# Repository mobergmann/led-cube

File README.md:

# led-cube

This repository contains:
1. main program: program that runs on the Pi, loads the configuration, and controls the LEDs
2. editor: program to create configuration by yourself
3. assets: files that are relevant for building the cubes
4. documentation: guide on how to assemble the cube, how to compile and install and use the main program and the editor

The documentation can be found in the `doc` folder.
A good entry point to the documentation is the [`doc/README.md`](./doc/README.md) file.

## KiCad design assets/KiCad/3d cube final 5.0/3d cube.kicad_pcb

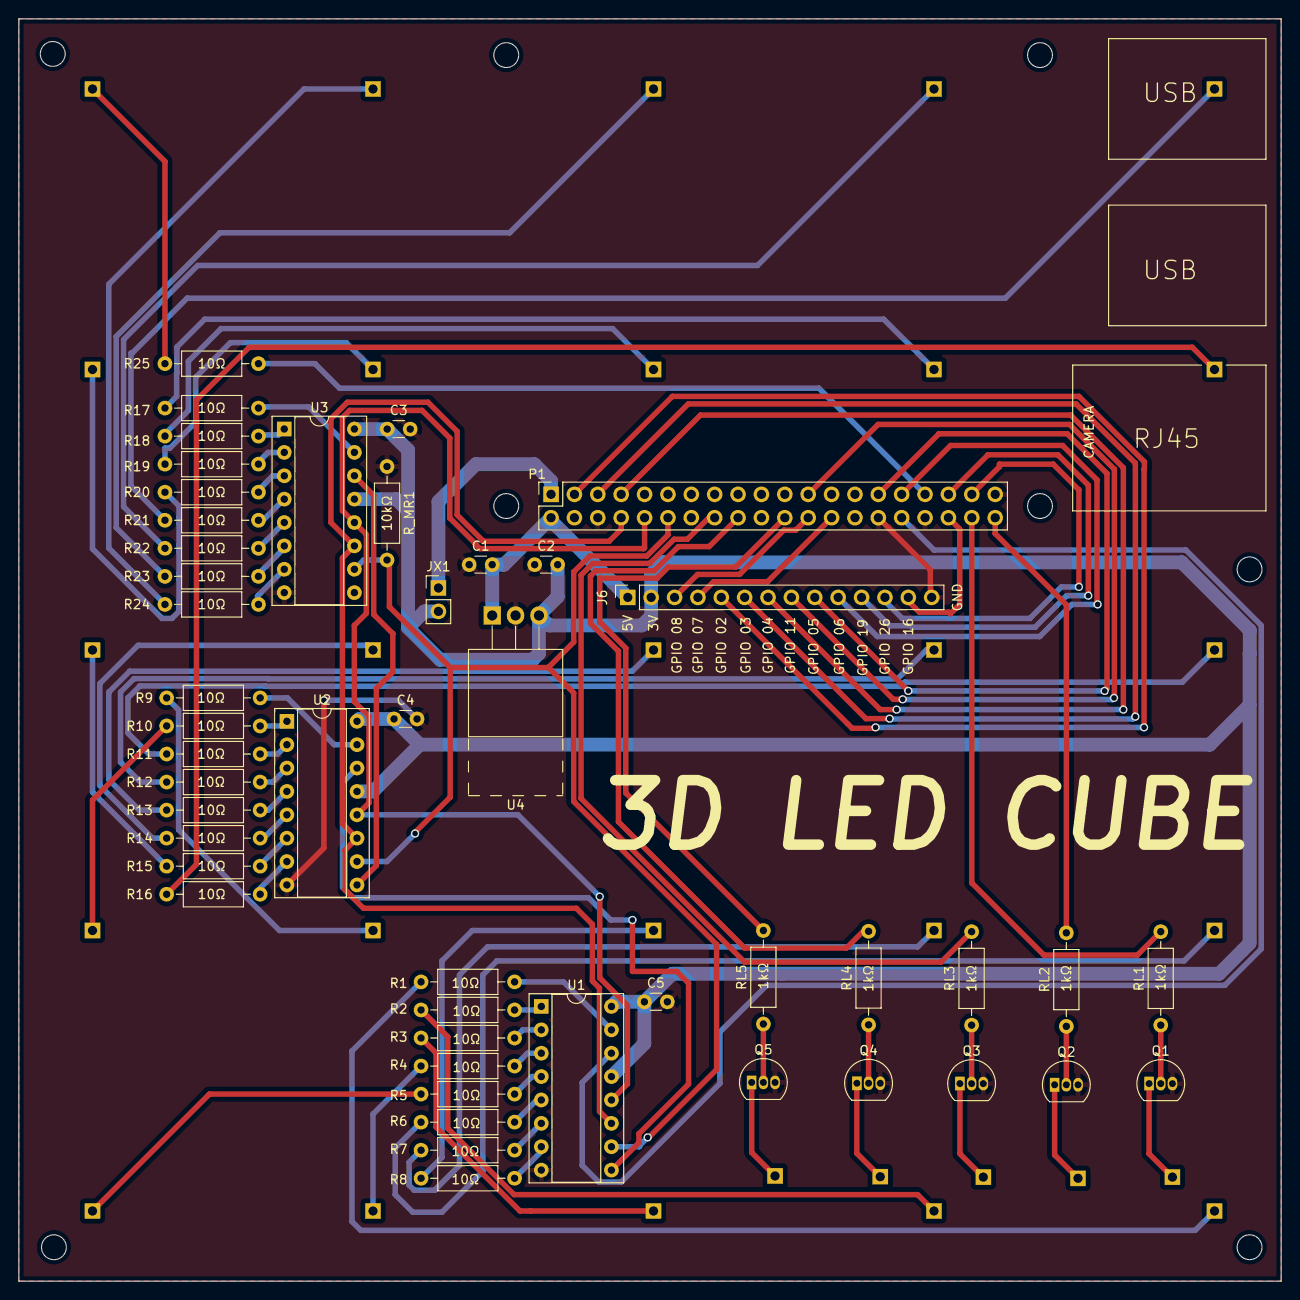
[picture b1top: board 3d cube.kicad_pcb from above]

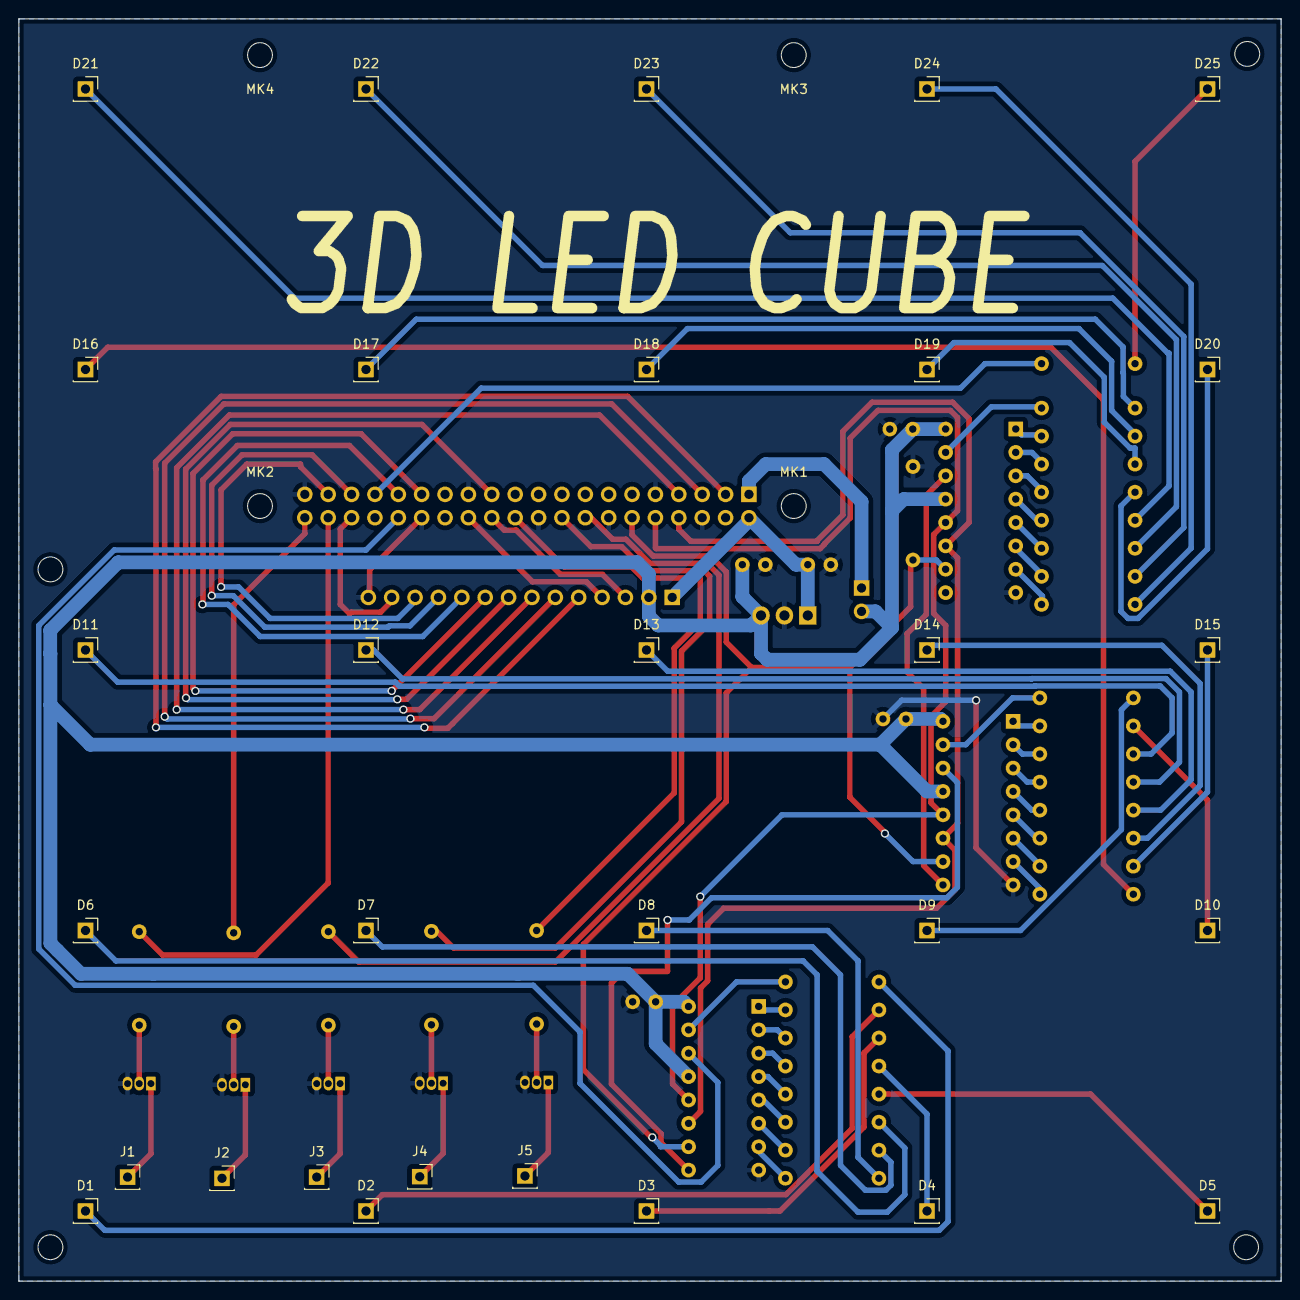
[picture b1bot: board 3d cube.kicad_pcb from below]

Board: 2 copper layers, 137.2 x 137.2 mm, 82 parts (34 on the bottom side), 86 nets.

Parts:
C1: 0.22μF; C_Disc_D3.0mm_W1.6mm_P2.50mm
C2: 10μF; C_Disc_D3.0mm_W1.6mm_P2.50mm
C3, C4, C5: 0.1μF; C_Disc_D3.0mm_W1.6mm_P2.50mm
D1, D2, D3, D4, D5, D6, D7, D8, D9, D10, D11, D12, D13, D14, D15, D16, D17, D18, D19, D20, D21, D22, D23, D24, D25: LED; PinSocket_1x01_P2.54mm_Vertical
J1: First Layer; PinSocket_1x01_P2.54mm_Vertical
J2: Second Layer; PinSocket_1x01_P2.54mm_Vertical
J3: Third Layer; PinSocket_1x01_P2.54mm_Vertical
J4: Fourth Layer; PinSocket_1x01_P2.54mm_Vertical
J5: Fifth Layer; PinSocket_1x01_P2.54mm_Vertical
J6: Conn_01x14_Female; PinSocket_1x14_P2.54mm_Vertical
JX1: 3V Bridge; PinHeader_1x02_P2.54mm_Vertical
MK1, MK2, MK3, MK4: M2.5; MountingHole_2.7mm_M2.5
P1: Conn_02x20_Odd_Even; PinSocket_2x20_P2.54mm_Vertical
Q1, Q2, Q3, Q4, Q5: 2N2222A; TO-92_Inline
R1, R2, R3, R4, R5, R6, R7, R8, R9, R10, R11, R12, R13, R14, R15, R16, R17, R18, R19, R20, R21, R22, R23, R24, R25: 10; R_Axial_DIN0207_L6.3mm_D2.5mm_P10.16mm_Horizontal
RL1, RL2, RL3, RL4, RL5: 1k; R_Axial_DIN0207_L6.3mm_D2.5mm_P10.16mm_Horizontal
R_MR1: 10k; R_Axial_DIN0207_L6.3mm_D2.5mm_P10.16mm_Horizontal
U1, U2, U3: 74HC595; DIP-16_W7.62mm_Socket
U4: LF15_TO220; TO-220-3_Horizontal_TabUp

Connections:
+3.3V: C2.1, C3.1, C4.1, C5.1, J6.2, JX1.2, U1.13 (~OE), U1.16 (VCC), U2.13 (~OE), U2.16 (VCC), U3.13 (~OE), U3.16 (VCC), U4.3 (VO)
+3.3V Rasberry: JX1.1, P1.1, P1.17
+5V: C1.1, J6.1, P1.2, P1.4, U4.1 (VI)
DS: P1.32, U1.14 (SER)
GND: C1.2, C2.2, C3.2, C4.2, C5.2, J6.14, P1.6, P1.9, P1.14, P1.20, P1.25, P1.30, P1.34, P1.39, Q1.3 (C), Q2.3 (C), Q3.3 (C), Q4.3 (C), Q5.3 (C), R_MR1.2, U1.8 (GND), U2.8 (GND), U3.8 (GND), U4.2 (GND)
GPIO2: J6.5, P1.3
GPIO3: J6.6, P1.5
GPIO4: J6.7, P1.7
GPIO5: J6.9, P1.29
GPIO6: J6.10, P1.31
GPIO7: J6.4, P1.26
GPIO8: J6.3, P1.24
GPIO11: J6.8, P1.23
GPIO16: J6.13, P1.36
GPIO19: J6.11, P1.35
GPIO26: J6.12, P1.37
Layer 1: P1.38, RL1.2
Layer 2: P1.40, RL2.2
Layer 3: P1.16, RL3.2
Layer 4: P1.18, RL4.2
Layer 5: P1.22, RL5.2
MR: P1.12, R_MR1.1, U1.10 (~SRCLR), U2.10 (~SRCLR), U3.10 (~SRCLR)
unnamed: D1.1 (K), R1.1
unnamed: D2.1 (K), R2.1
unnamed: D3.1 (K), R3.1
unnamed: D4.1 (K), R4.1
unnamed: D5.1 (K), R5.1
unnamed: D6.1 (K), R6.1
unnamed: D7.1 (K), R7.1
unnamed: D8.1 (K), R8.1
unnamed: D9.1 (K), R9.1
unnamed: D10.1 (K), R10.1
unnamed: D11.1 (K), R11.1
unnamed: D12.1 (K), R12.1
unnamed: D13.1 (K), R13.1
unnamed: D14.1 (K), R14.1
unnamed: D15.1 (K), R15.1
unnamed: D16.1 (K), R16.1
unnamed: D17.1 (K), R17.1
unnamed: D18.1 (K), R18.1
unnamed: D19.1 (K), R19.1
unnamed: D20.1 (K), R20.1
unnamed: D21.1 (K), R21.1
unnamed: D22.1 (K), R22.1
unnamed: D23.1 (K), R23.1
unnamed: D24.1 (K), R24.1
unnamed: D25.1 (K), R25.1
unnamed: J1.1, Q1.1 (E)
unnamed: J2.1, Q2.1 (E)
unnamed: J3.1, Q3.1 (E)
unnamed: J4.1, Q4.1 (E)
unnamed: J5.1, Q5.1 (E)
unnamed: Q1.2 (B), RL1.1
unnamed: Q2.2 (B), RL2.1
unnamed: Q3.2 (B), RL3.1
unnamed: Q4.2 (B), RL4.1
unnamed: Q5.2 (B), RL5.1
unnamed: R1.2, U1.15 (QA)
unnamed: R2.2, U1.1 (QB)
unnamed: R3.2, U1.2 (QC)
unnamed: R4.2, U1.3 (QD)
unnamed: R5.2, U1.4 (QE)
unnamed: R6.2, U1.5 (QF)
unnamed: R7.2, U1.6 (QG)
unnamed: R8.2, U1.7 (QH)
unnamed: R9.2, U2.15 (QA)
unnamed: R10.2, U2.1 (QB)
unnamed: R11.2, U2.2 (QC)
unnamed: R12.2, U2.3 (QD)
unnamed: R13.2, U2.4 (QE)
unnamed: R14.2, U2.5 (QF)
unnamed: R15.2, U2.6 (QG)
unnamed: R16.2, U2.7 (QH)
unnamed: R17.2, U3.15 (QA)
unnamed: R18.2, U3.1 (QB)
unnamed: R19.2, U3.2 (QC)
unnamed: R20.2, U3.3 (QD)
unnamed: R21.2, U3.4 (QE)
unnamed: R22.2, U3.5 (QF)
unnamed: R23.2, U3.6 (QG)
unnamed: R24.2, U3.7 (QH)
unnamed: U1.9 (QH'), U2.14 (SER)
unnamed: U2.9 (QH'), U3.14 (SER)
Pin 25: P1.33, R25.2
SHCP: P1.8, U1.11 (SRCLK), U2.11 (SRCLK), U3.11 (SRCLK)
STCP: P1.10, U1.12 (RCLK), U2.12 (RCLK), U3.12 (RCLK)

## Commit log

2022-06-08 initial
2022-06-17 multiple code bases
2022-06-17 removed build files
2022-06-17 compilable
2022-06-17 notes on which pin used
2022-06-17 gitignore path optimized
2022-06-17 WIP: led software
2022-06-18 added KiCad folder
2022-06-18 converted to class
2022-06-18 removed unnecessary import
2022-06-18 WIP cube UI
2022-06-18 WIP: added UI
2022-06-19 fixed yellow leds
2022-06-19 workable software
2022-06-19 added test-1
2022-06-19 wip: added delta time for max frame time and a test script
2022-06-20 added play sequenze button
2022-06-20 delta time implementation
2022-06-22 rotate with right mouse button, leds in the json files now in the right sequenze
2022-06-22 adjusted to new parser
2022-06-22 removed old targets
2022-06-22 fixed comment messages
2022-06-22 layer test json
2022-06-22 fix json saving
2022-06-22 change data in json to layers
2022-06-22 layer-5 test json
2022-06-22 changed data.json name
2022-06-22 fixed issues (don't know which, look yourself)
2022-06-22 wip: reverse pins and lines
2022-06-23 fixed reverse error
2022-08-03 wip: fixes issues
2022-08-04 added reset test program
2022-08-04 fixed skipp of input
2022-08-05 wip: reset test
2022-08-05 formatted
2022-08-05 reset enhancements
2022-08-05 added dependencies to readme
2022-08-11 added a polling skeleton for pressing buttons
2022-08-11 removed added extra program
2022-08-15 wip readme
2022-08-15 added base project
2022-08-15 added gitignore
2022-08-15 added file documentation
2022-08-15 removed old json files
2022-08-15 ignored clion and vscode files
2022-08-15 moved extra files into assets folder
2022-08-15 renamed notes
2022-08-15 added documentation
2022-08-15 added line numbers to i/o pins
2022-08-15 added Qt3DCore binaries
2022-08-15 added a main window
2022-08-15 added a basic ui (not functional)
2022-08-16 added bluetooth function declaration
2022-08-16 added todo to buttons, which doesnt work
2022-08-17 added bluetooth class
2022-08-17 fixed compilation error
2022-08-17 added is_rising_edge declaration
2022-08-17 added a button test program
2022-08-17 fixed order of pins
2022-08-17 button configuration
2022-08-17 wip: moving files outside
2022-08-18 added blink thread for bluetooth pairing led
2022-08-18 code refactoring
2022-08-18 reset test improvements and fixed an issue in main program
2022-08-18 removed obsolete buttons program
2022-08-19 added threads to cmake linking
2022-08-19 removed buttons from cmake, as file doesn't exists anymore
2022-08-19 removed reset test program
2022-08-19 applied reset to main
2022-08-19 update dependency
2022-08-19 updated readme button pins
2022-08-19 added example json files
2022-08-19 wip: button functionality
2022-08-19 button functionality
2022-08-19 moved reset call to each layer
2022-08-19 changed path to files
2022-08-19 fixed reset
2022-08-19 files are now pulled
2022-08-19 added filesystem to cmake
2022-08-19 added a filesystem test program
2022-08-19 applied the fs test results to main
2022-08-19 removed fs files
2022-08-20 added comment to class member
2022-08-20 added button class
2022-08-20 applied button class to main program
2022-08-20 default led-cube configuration path definition
2022-08-21 wip: cube rendering
2022-08-22 added const to static Button variable
2022-08-22 fixed bluetooth button crashing program
2022-08-22 added cout for cube configuration
2022-08-22 removed exil file
2022-08-22 print first configuration
2022-08-22 restructior falling edge method
2022-08-22 change filepath in cube/main.py add blink_layer.json
2022-08-22 bluetooth order changed, to update after blink
2022-08-22 changed from copy for loop to direct access loop
2022-08-22 added new test files for the cube
2022-08-22 remouve button bounce
2022-08-22 change to falling edge
2022-08-22 finished button bounce
2022-08-22 fixes initialize issues
2022-08-22 removed (sebs) file
2022-08-22 changed order of main methods
2022-08-22 added edge case check and removed iterators from next and previous
2022-08-22 fixed next and previous buttons
2022-08-22 undo: fixed next and previous buttons
2022-08-22 undo: undo: fixed next and previous buttons
2022-08-22 fixed previous button
2022-08-22 fixed accidentally decrementing in next
2022-08-22 added optimisation
2022-08-22 fixed rotation not working
2022-08-22 parsing layout after each button press
2022-08-22 added destructor for main
2022-08-22 removed shadow copy
2022-08-22 removed unnecessary close
2022-08-22 wip: error hunting
2022-08-22 wip: added test program
2022-08-22 wip: test program
2022-08-23 check if the frames have changed and then quit loop
2022-08-23 uncomment reset call in set_leds, as it didn't cause the weird led behaviour
2022-08-23 added print statement and removed revert
2022-08-23 dynamic line name acquisition
2022-08-23 layer python test program
2022-08-23 added input dialogue for test
2022-08-23 added store for cube
2022-08-23 fixed python program
2022-08-23 implemented layer test in c++
2022-08-23 removed print
2022-08-23 fixed layer 5 being enabled
2022-08-23 moved store after turning off layer, so it will be displayed
2022-08-24 wip: does this layer on/ off work?
2022-08-24 git revert to working solution
2022-08-24 sequence test program
2022-08-24 wip: test activation of two pins on two layers
2022-08-24 special pin only turn off on store (with/ like all the other pins)
2022-08-24 wip: hopefully fix all our layer 1 is on and glows, but 5 also glows problems
2022-08-24 reduce the off time to 5 writes
2022-08-24 fixed special pin always on
2022-08-24 fixed array indexing last elem with out-of-bounds
2022-08-24 changed to qt version 6
2022-08-24 removed previous (commented) cmake
2022-08-25 moved from 3d to quick
2022-08-26 added ScrollView for Frames
2022-08-26 rotationiion cube done
2022-08-27 led on/off now functioning
2022-08-27 cube rotation finished
2022-08-27 clean up code
2022-08-27 now going for opengl
2022-08-27 new frame/delete frame button working
2022-08-28 play button working
2022-08-28 clean up
2022-08-28 wip: opengl
2022-08-28 save to JSON works
2022-08-28 preperation for the open button
2022-08-28 open Json button now working/ version 1.0 working
2022-08-29 wip: reverse pins
2022-08-29 wip: removed compilation error
2022-08-29 wip: fixed condition
2022-08-29 wip: loop conditions
2022-08-29 wip: fix segfault
2022-08-29 wip: fix loop performance
2022-08-29 fix orientation to the real cube
2022-08-29 added front indicator
2022-08-29 wip: flipped x- and y-axis
2022-08-29 shift buttons working
2022-08-29 shift button behaviour
2022-08-29 bluetooth class, removed test scripts, still in merge?
2022-08-29 finished random and magic button and copy button
2022-08-30 updated user pin usage in table
2022-08-30 wip: added an installation script file
2022-08-31 moved into src and include folder and deleted test files
2022-08-31 added file-transfer class
2022-08-31 changed data folders moved folder init into main
2022-08-31 removed static from function, because it isn't meant to be
2022-08-31 fixed wrong file paths
2022-08-31 changed file system type in mount to vfat, aka usb
2022-08-31 added function call to update_file_list
2022-08-31 override existing files
2022-08-31 added data to install script
2022-09-02 fixed typo in dependencies
2022-09-05 new file/ WIP gameoflife
2022-09-05 added installation files and assets
2022-09-05 tried dependency libgpiod
2022-09-05 finalized build
2022-09-05 finalized install script
2022-09-05 added binaries rename to gitignore
2022-09-05 commented in download of dependencie
2022-09-05 finalisation
2022-09-05 uncommented apt commands
2022-09-05 added install script
2022-09-05 resolve minor issues
2022-09-05 fixed typo
2022-09-05 removed .idea folder
2022-09-05 added clear
2022-09-05 modified README files
2022-09-05 cleaned all unneccesarry files
2022-09-06 fixed cp
2022-09-06 download ibgpiod
2022-09-06 download libpiod
2022-09-06 added debug
2022-09-06 hopefully fixed blink thread not ending bug
2022-09-06 implemented a long press functionality
2022-09-06 implemented actual deletion
2022-09-07 fixed not blinking
2022-09-07 made destructor virtual
2022-09-07 only one transfer function
2022-09-07 pls work now
2022-09-07 fixed mount path
2022-09-07 fixed file transfer
2022-09-07 @seb8299 fix of is_falling_edge()
2022-09-07 fixed button trigger
2022-09-07 added new configs
2022-09-07 fixed buttons not pressed
2022-09-07 fixed blink not stopping, when no mount
2022-09-12 cleanup/ version 1.0
2022-09-12 change savepath to downloadpath
2022-09-12 moved inner editor folder one down and deleted old folder
2022-09-12 added README for @seb8299 to populate
2022-09-15 WIP: README
2022-09-21 Readme.me Button behaviour
2022-09-21 changed the open and save file buttons to explorer
2022-09-21 update Readme from last commit
2022-09-21 now name will be shown when file open/ cleanup from last commits
2022-09-21 add links to Readme
2022-09-21 fixed inclusion of build files
2022-09-21 removed bad exampples
2022-09-21 renamed waterdrop
2022-09-21 renamed example configuration folder
2022-10-05 renamed KiCad to PCB
2022-10-05 removed asset examples and moved count-numbers to install foler
2022-10-05 added 3d print files
2022-10-05 wip: doc
2022-10-05 removed local readmes
2022-10-05 translated the doc to english
2022-10-05 added further install informations
2022-10-05 fixed mdcode error
2022-10-06 Update assemble.md
    added components, pcb, wire mesh and buttons
2022-10-06 added image to doc
